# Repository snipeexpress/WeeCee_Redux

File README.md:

<!-- markdownlint-disable MD031 -->

# WeeCee Redux

**WeeCee Redux** is a hardware clone of Rasteri’s **WeeCee v0.3**, enhanced with a variety of improvements for modern usability, better component choices, and more robust design.

## Key Improvements

1. **HIDman Integration**  
   
   Replaced the legacy PS/2 port with [HIDman](https://github.com/Rasteri/HIDman), enabling support for modern USB HID devices via USB-to-PS/2 translation.

2. **Improved Audio Circuitry**  
   
   Refined the CS4237B circuitry for enhanced signal filtering and improved ground plane separation for cleaner audio performance.

3. **USB-C Power + On/Off Controller**  
   
   Replaced the micro-USB power input with USB-C. Integrated a **MAX16054** on/off controller for reliable power switching.

4. **On-Board PC Speaker**  
   
   Added a miniature PC speaker directly on the board. Can be disabled via jumper if not needed.

5. **Cost-Optimized Connectors**  
   
   Swapped out the MicroSD and audio output connectors for more affordable variants — the same ones used on Eivind Bøhler’s [TinyLlama](https://github.com/eivindbohler/TinyLlama).

6. **Enhanced Front Panel**  
   
   - Added a power button header for direct connection  
   - Added a reset button  
   - Added a power LED to indicate system status

7. **SD Card Activity Indicator**  
   
   Included circuitry and a front-panel LED to show real-time SD card activity.

8. **RTC Battery Support**  
   
   Added support for a **CR1220** coin cell battery to maintain Real-Time Clock settings.

## Enclosure Notes

This revision still fits the original enclosure used in Rasteri’s WeeCee v0.3. However, due to the added ports and indicators, **updated front and rear panels are required** for proper alignment.

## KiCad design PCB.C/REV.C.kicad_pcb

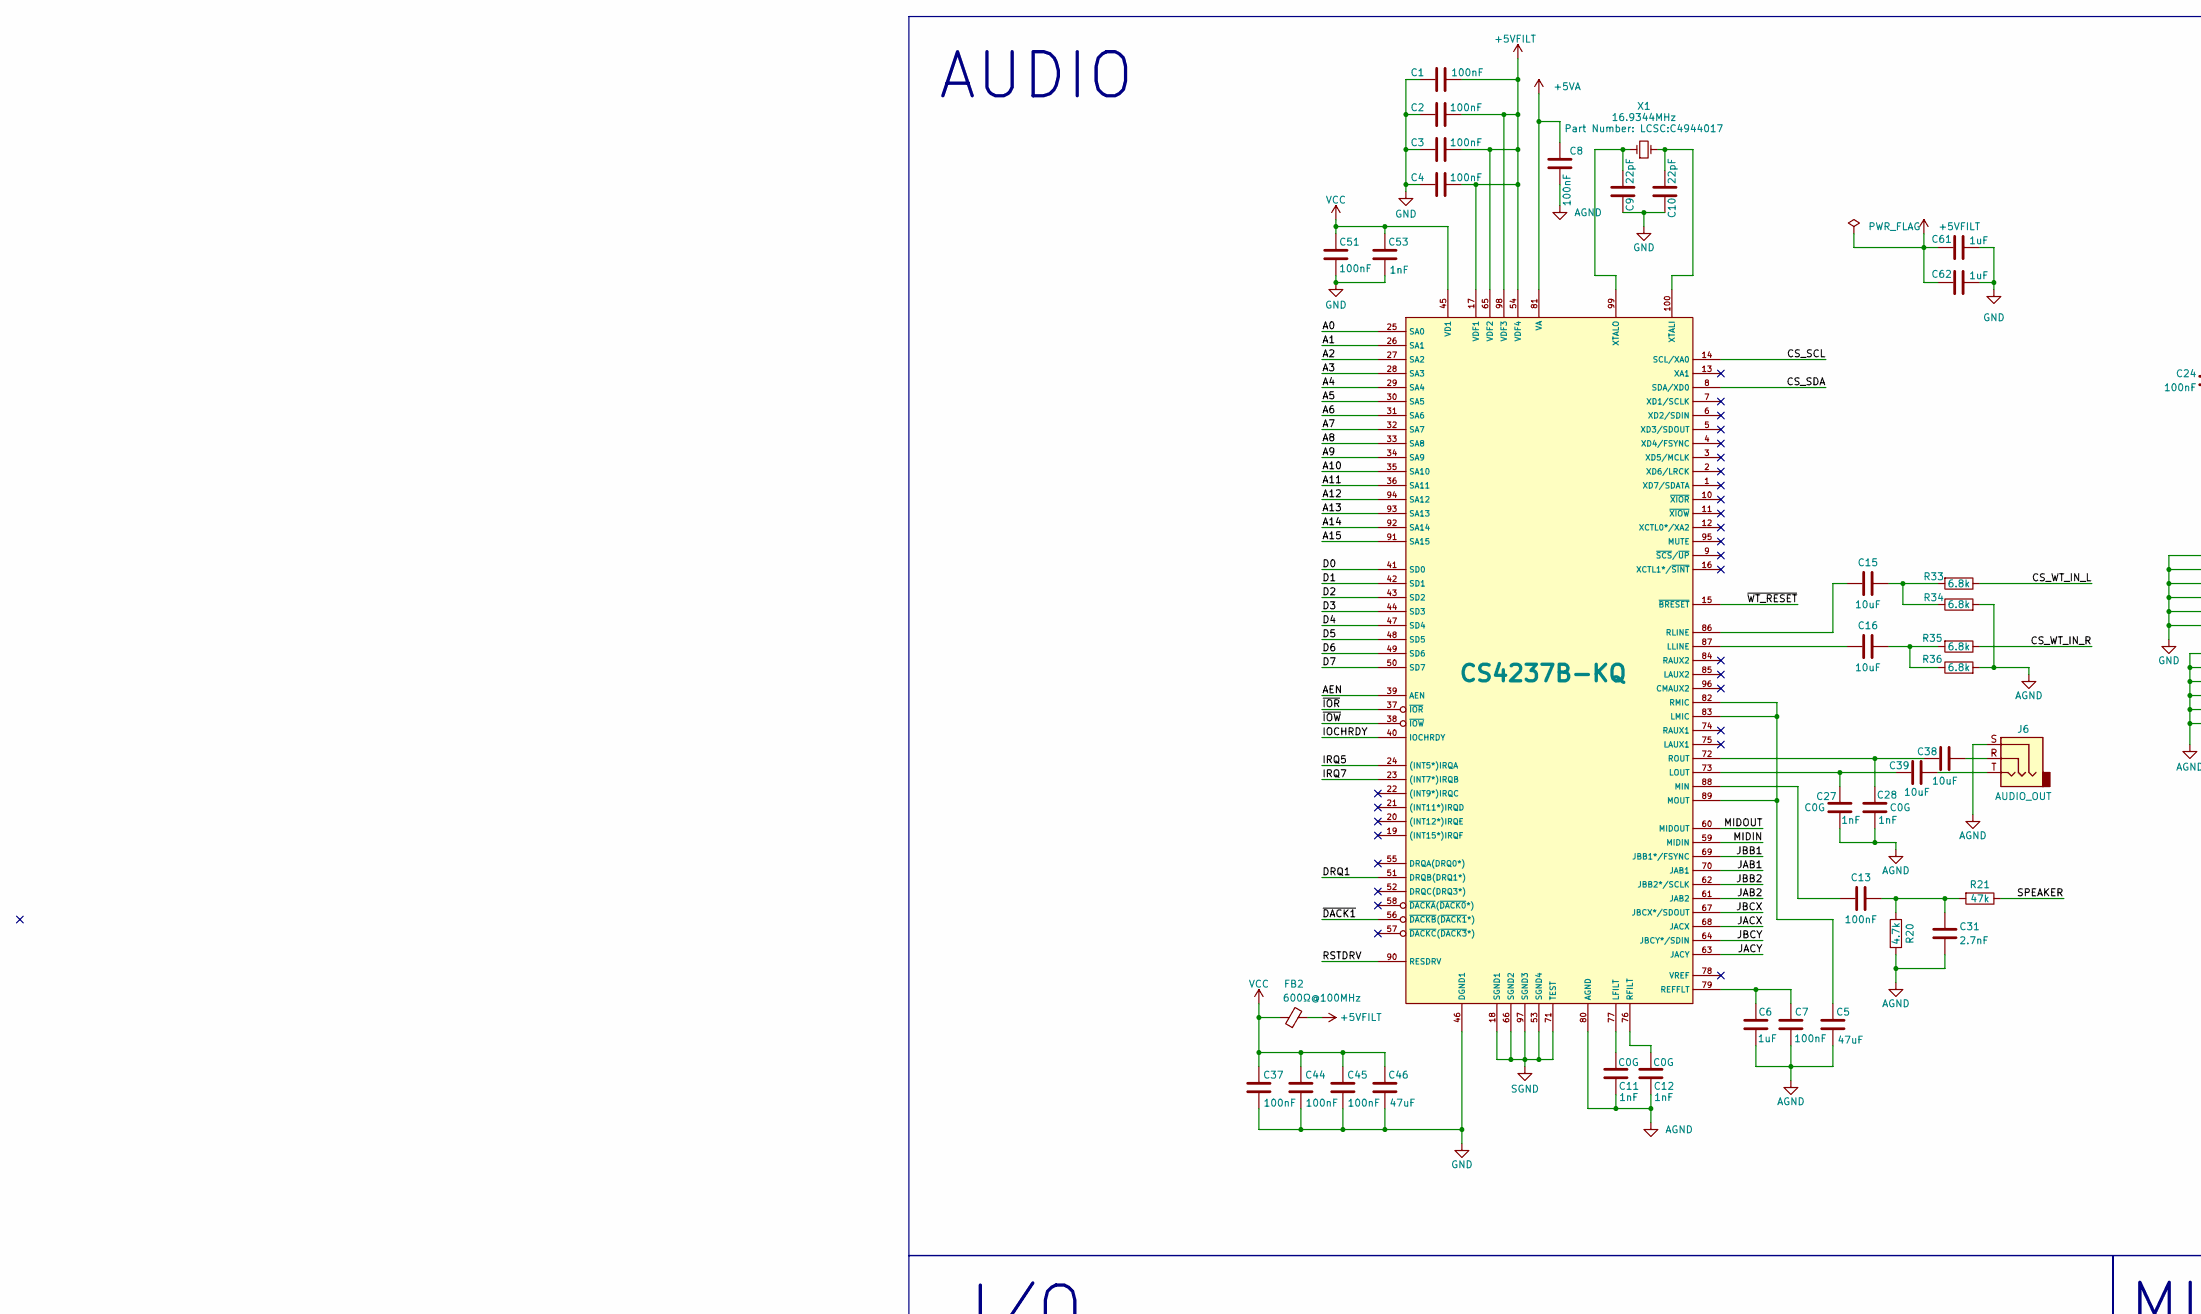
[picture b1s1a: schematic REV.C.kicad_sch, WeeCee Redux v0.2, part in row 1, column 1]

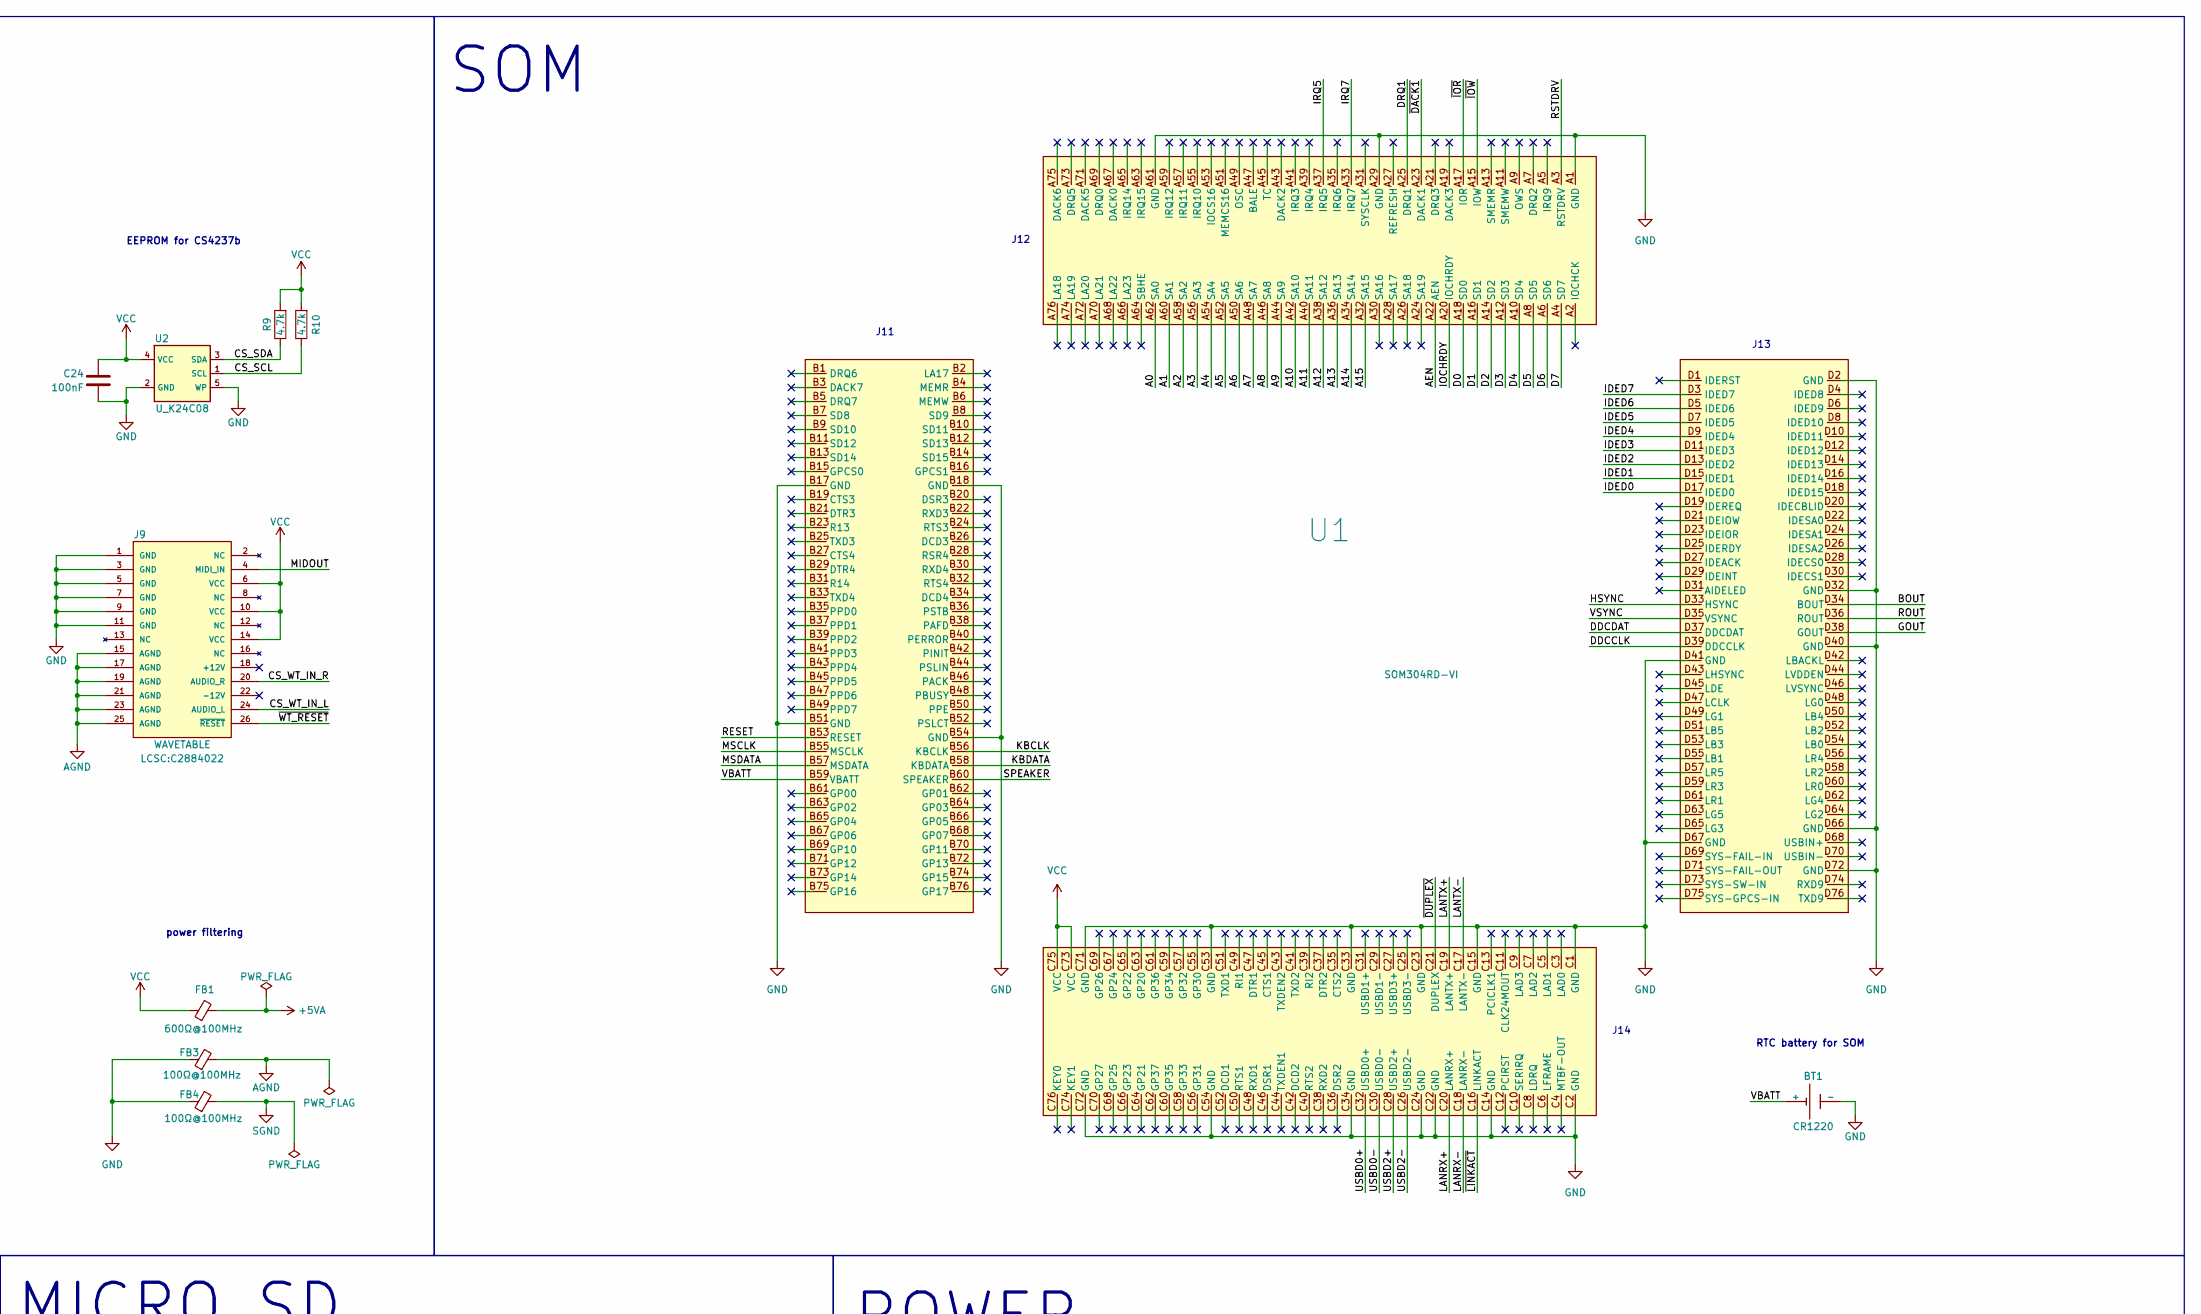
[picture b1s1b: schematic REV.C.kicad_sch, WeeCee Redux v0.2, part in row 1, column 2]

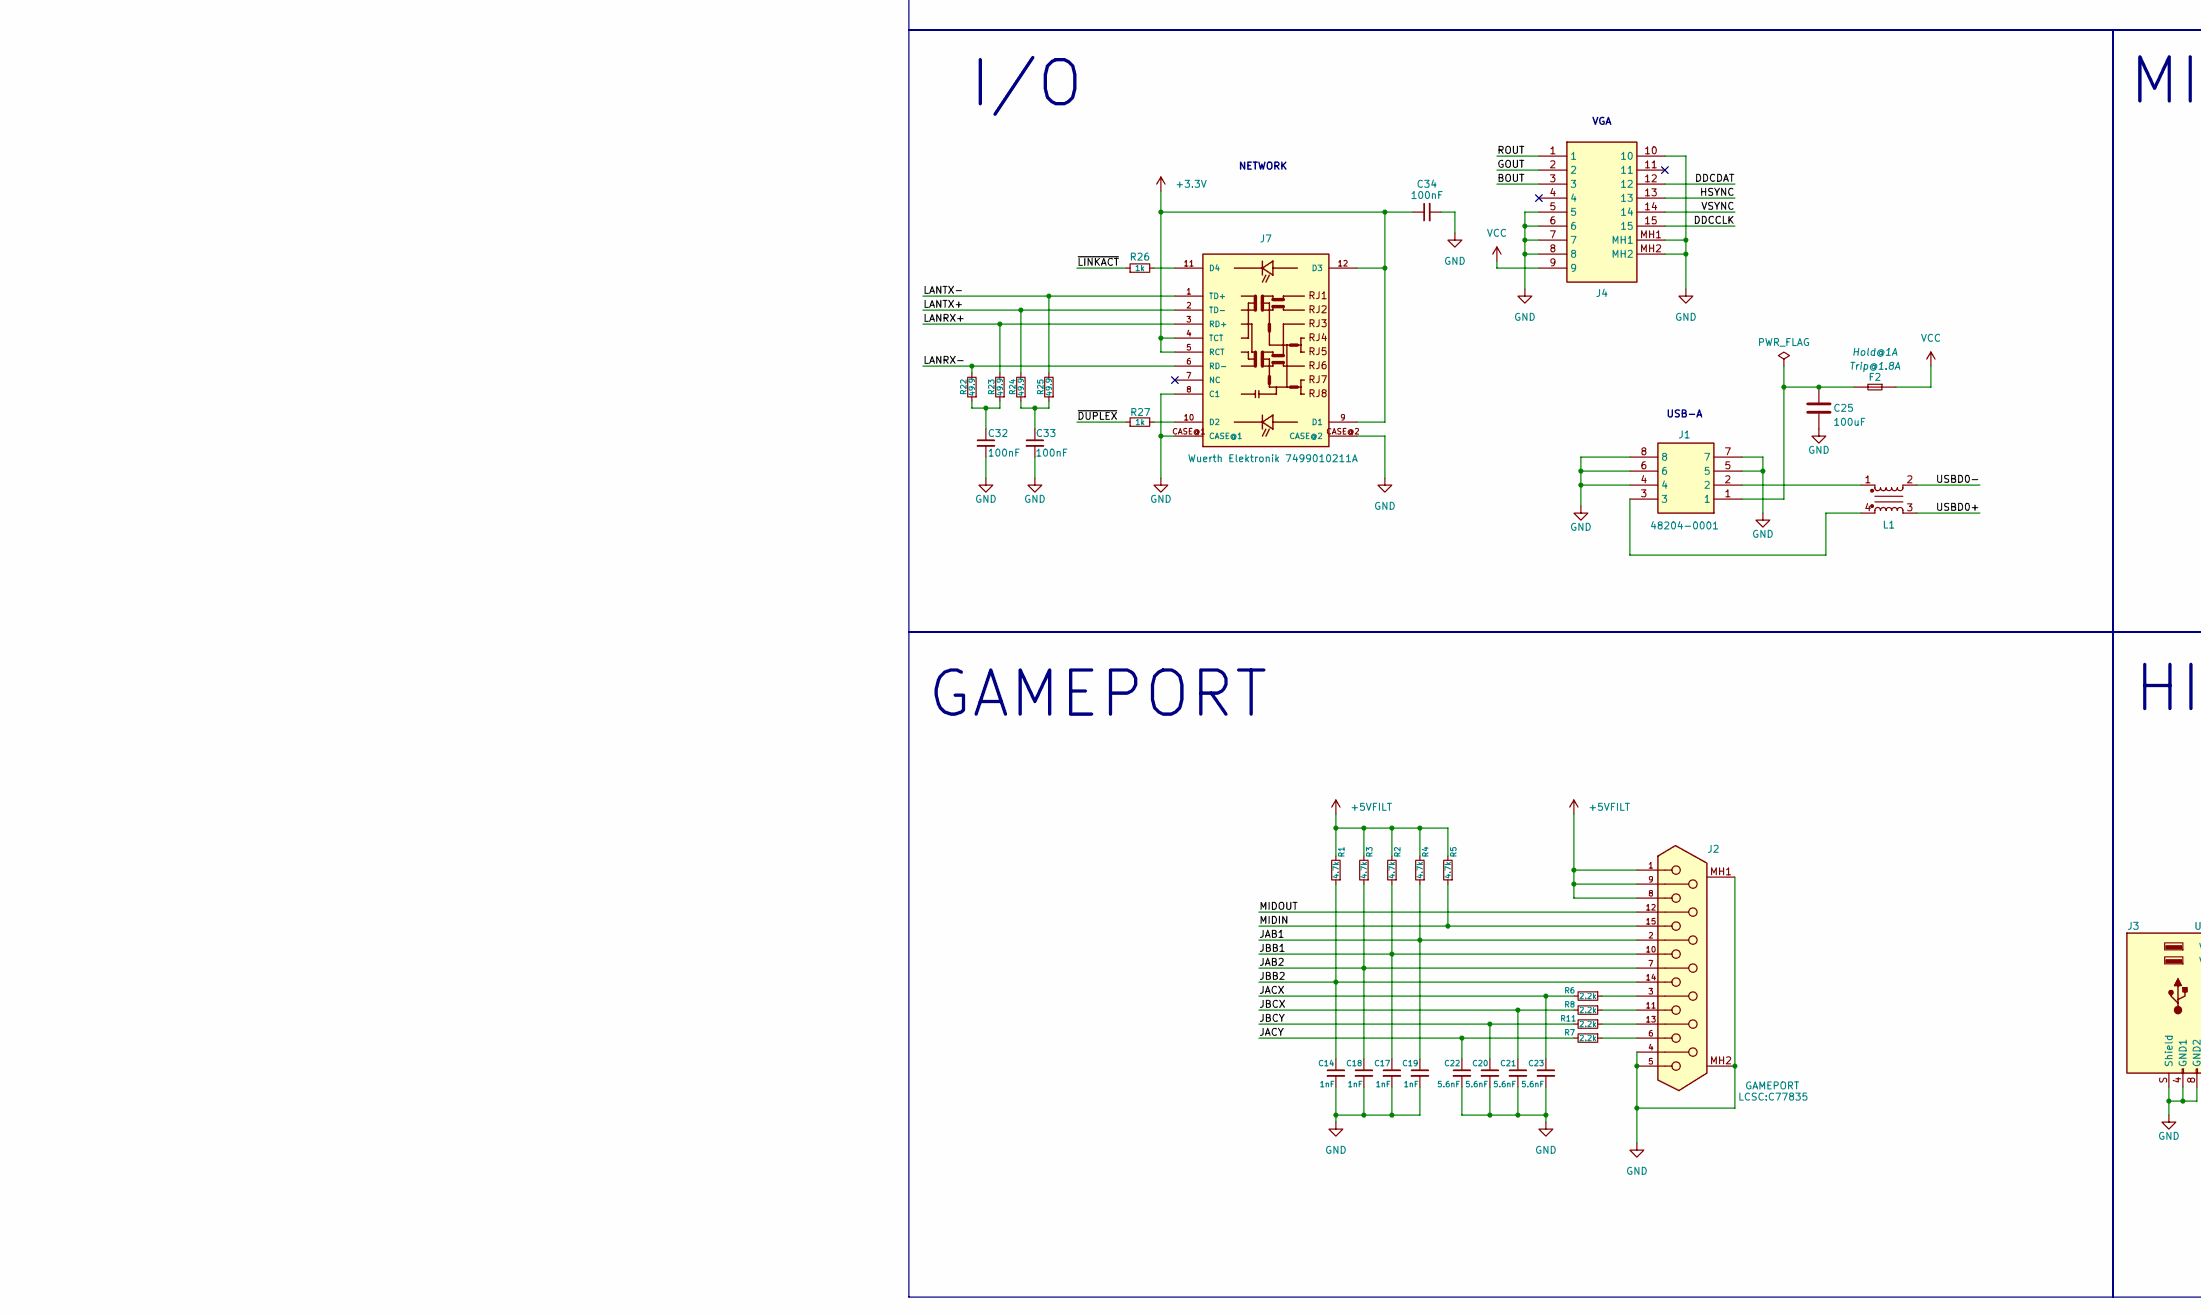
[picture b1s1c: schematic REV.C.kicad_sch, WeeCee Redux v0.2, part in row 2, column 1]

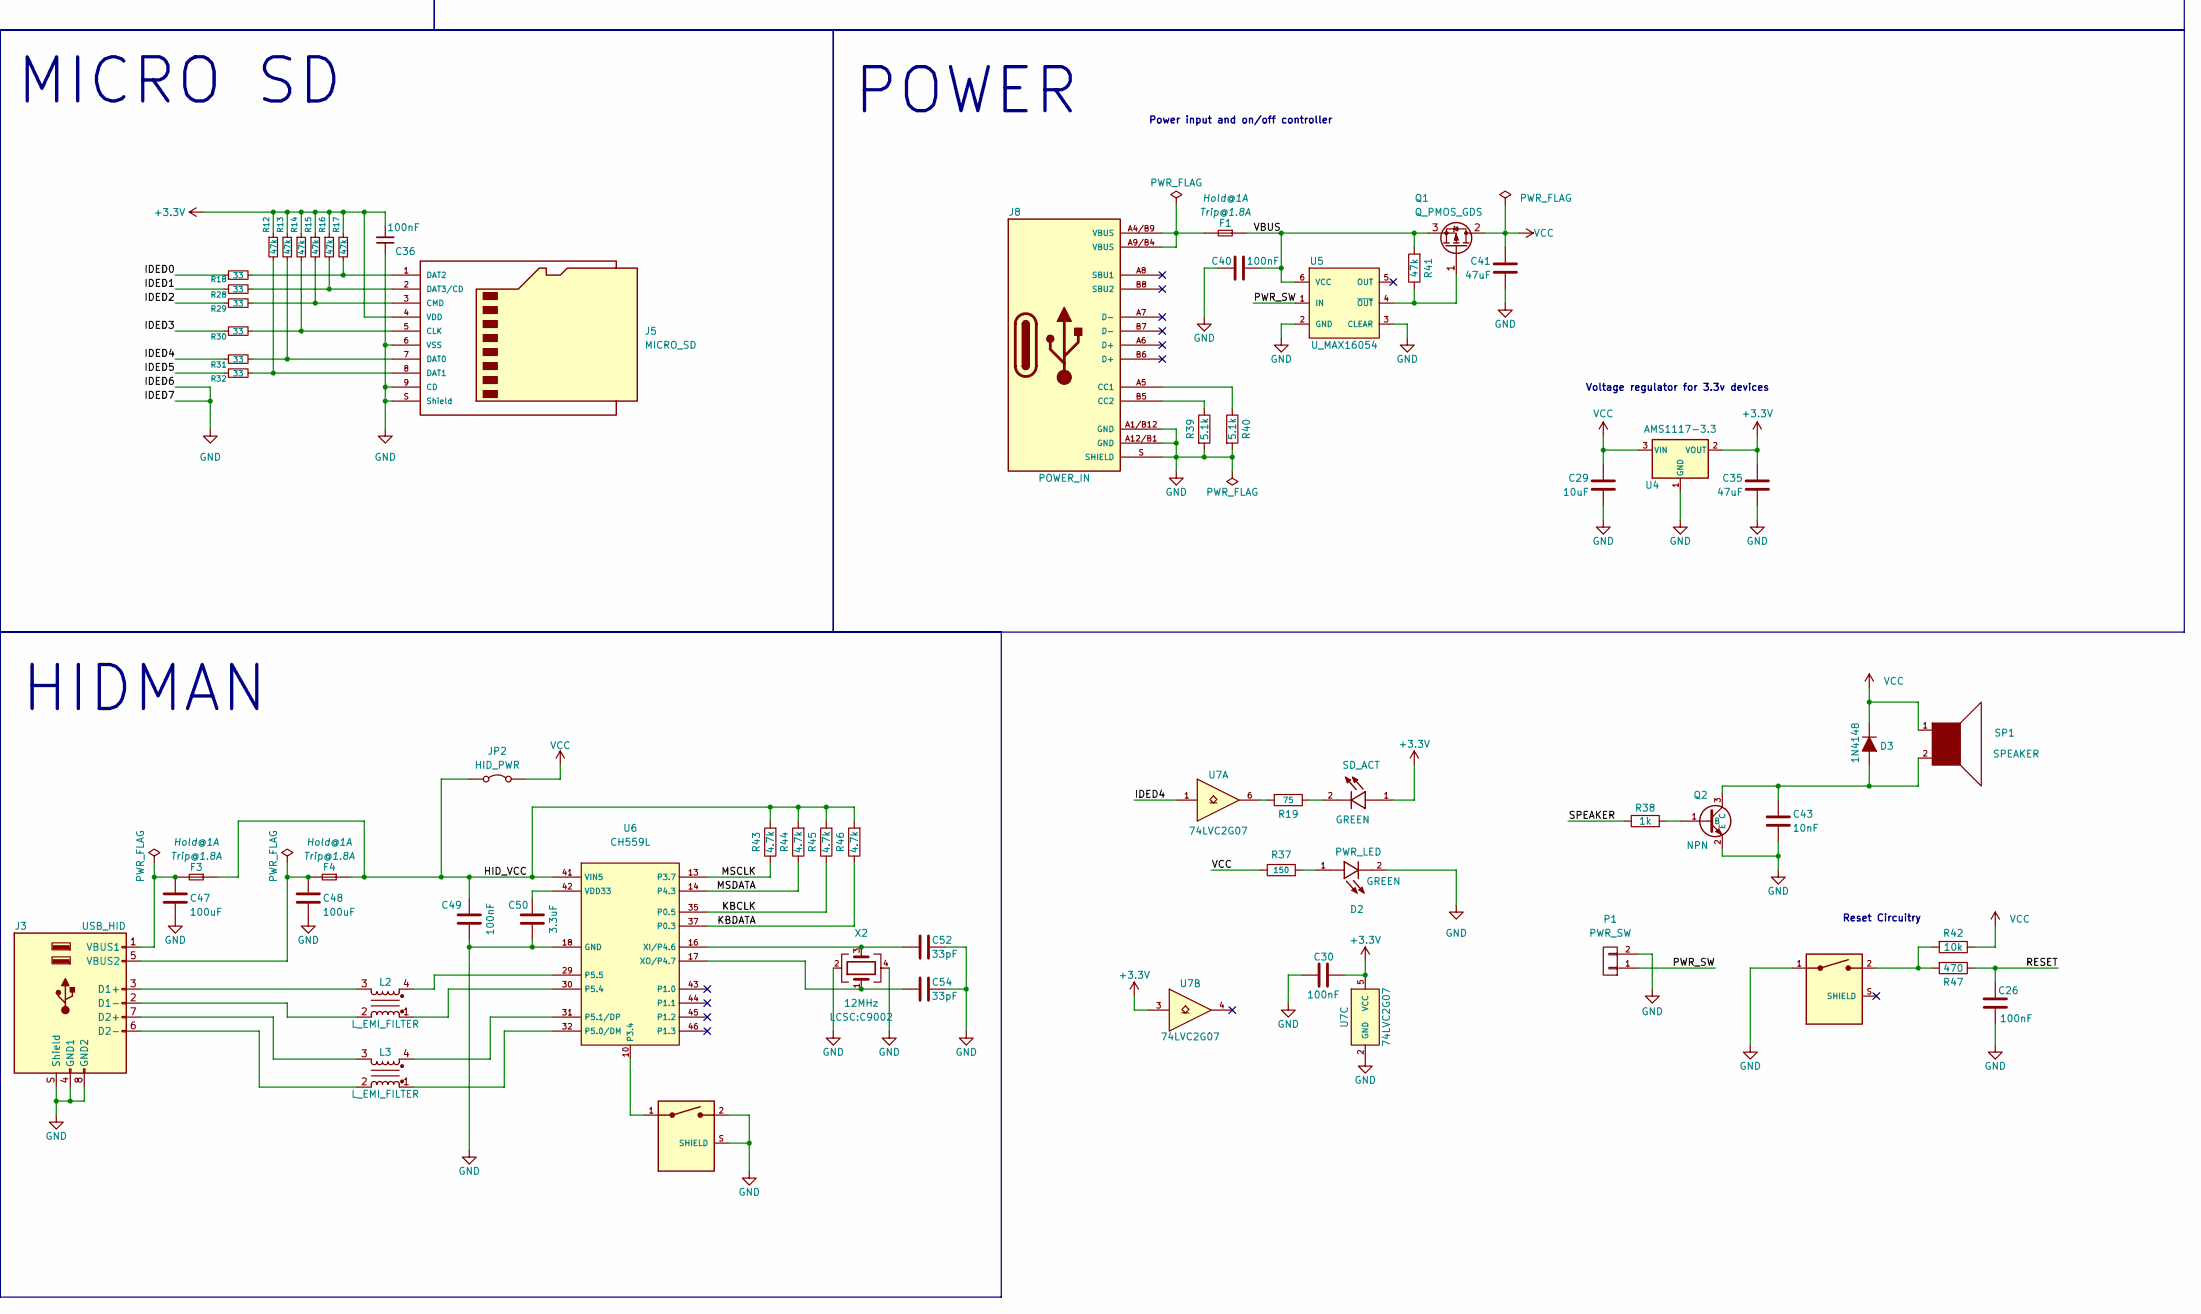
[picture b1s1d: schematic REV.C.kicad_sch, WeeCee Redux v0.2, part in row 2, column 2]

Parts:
BT1: CR1220; BATT-1220-03; Part Number LCSC:C964818
C1, C2, C3, C4, C7, C8, C13, C24, C26, C30, C32, C33, C34, C36, C37, C40, C44, C45, C49, C51: 100nF; C_0603_1608Metric; Part Number DIGIKEY:C0603C104K3RACTU
C5, C35, C41, C46: 47uF; C_1206_3216Metric; Part Number DIGIKEY:C1206C476M8PACTU
C6, C61, C62: 1uF; C_1206_3216Metric; Part Number DIGIKEY:C1206C105K3RACTU
C9, C10: 22pF; C_0603_1608Metric; Part Number DIGIKEY:C0603C220J8GACTU
C11, C12, C27, C28: 1nF; C_0603_1608Metric; Part Number DIGIKEY:GRM1885C1H102JA01D
C14, C17, C18, C19: 1nF; C_0603_1608Metric; Part Number DIGIKEY:C0603C102K3RACTU
C15, C16: 10uF; C_0603_1608Metric; Part Number DIGIKEY:C0603C106M9PACTU
C20, C21, C22, C23: 5.6nF; C_0603_1608Metric; Part Number DIGIKEY:C0603C562K3RACTU
C25, C47, C48: 100uF; C_1206_3216Metric; Part Number DIGIKEY:GRM31CR61A107MEA8K
C29: 10uF; C_1206_3216Metric; Part Number DIGIKEY:C1206C106K4PACTU
C31: 2.7nF; C_0603_1608Metric; Part Number DIGIKEY:C0603C272K5RACTU
C38, C39: 10uF; C_1206_3216Metric; Part Number DIGIKEY: C1206C106K4PACTU
C43: 10nF; C_0603_1608Metric; Part Number DIGIKEY:C0603C103K5RACTU
C50: 3.3uF; C_0603_1608Metric; Part Number DIGIKEY:C0603C335M9PACTU
C52, C54: 33pF; C_0603_1608Metric; Part Number LCSC:C1663
C53: 1nF; C_1206_3216Metric; Part Number DIGIKEY:C0603C102K5RACTU
D1: SD_ACT; LED_LTST-S220KSKT; Part Number DIGIKEY:LTST-S220KGKT
D2: PWR_LED; LED_LTST-S220KSKT; Part Number DIGIKEY:LTST-S220KGKT
D3: 1N4148; D_SOD-323F; Part Number DIGIKEY:1N4148WS-7-F
F1, F2, F3, F4: F; Fuse_0603_1608Metric_no_outline; Part Number DIGIKEY:0603L100SLYR
FB1, FB2: 600Ω@100MHz; R_0805_2012Metric; Part Number DIGIKEY:MPZ2012S601ATD25
FB3, FB4: 100Ω@100MHz; R_0805_2012Metric; Part Number DIGIKEY:MPZ2012S101AT000
J1: 48204-0001; USB-A_1P_VERTICAL; Part Number DIGIKEY:0482040001
J2: GAMEPORT; 57478454; Part Number LCSC:C77835
J3: USB_HID; USB-A_2P_STACKED; Part Number DIGIKEY:C12049
J4: VGA_IN; 634015263032; Part Number DIGIKEY:634-015-263-032
J5: MICRO_SD; MicroSD_TF01A_overhang; Part Number LCSC:C91145
J6: AUDIO_OUT; J_AUDIO35_C95463; Part Number LCSC:C95463
J7: Wuerth Elektronik 7499010211A; NIC_single_port_TH; Part Number DIGIKEY:7499010211A
J8: POWER_IN; USB-C_31-M-12; Part Number LCSC:C165948
J9: WAVETABLE; J_CONN_02X13; Part Number LCSC:C2884022
JP2: HID_PWR; SolderJumper-2_P1.3mm_Open_RoundedPad1.0x1.5mm
L1, L2, L3: L_EMI_FILTER; L_EMI_FILTER_MCM2012B900GBE; Part Number DIGIKEY:MCM2012B900GBEDG
P1: PWR_SW; PinHeader_1x02_P2.00mm_Horizontal; Part Number ALIEXPRESS
Q1: Q_PMOS_GDS; Q_PFET_ENH_SOT-23-3; Part Number DIGIKEY:DMP3099L-7
Q2: NPN; Q_PFET_ENH_SOT-23-3; Part Number LCSC:C2146
R1, R2, R3, R4, R5, R9, R10, R20, R43, R44, R45, R46: 4.7k; R_0603_1608Metric; Part Number DIGIKEY:RC0603FR-074K7L
R6, R7, R8, R11: 2.2k; R_0603_1608Metric; Part Number DIGIKEY:RC0603FR-072K2L
R12, R13, R14, R15, R16, R17, R21, R41: 47k; R_0603_1608Metric; Part Number DIGIKEY:RC0603FR-0747KL
R18, R28, R29, R30, R31, R32: 33; R_0603_1608Metric; Part Number DIGIKEY:RC0603JR-0733RL
R19: 75; R_0603_1608Metric; Part Number DIGIKEY:RC0603JR-0775RL
R22, R23, R24, R25: 49.9; R_0603_1608Metric; Part Number DIGIKEY:RC0603FR-0749R9L
R26, R27, R38: 1k; R_0603_1608Metric; Part Number DIGIKEY:RC0603FR-071KL
R33, R34, R35, R36: 6.8k; R_0603_1608Metric; Part Number DIGIKEY:RC0603JR-076K8L
R37: 150; R_0603_1608Metric; Part Number DIGIKEY:RC0603FR-07150RL
R39, R40: 5.1k; R_0603_1608Metric; Part Number DIGIKEY:RC0603FR-075K1L
R42: 10k; R_0603_1608Metric; Part Number DIGIKEY:RC0603FR-0710KL
R47: 470; R_0603_1608Metric; Part Number DIGIKEY:RC0603JR-07470RL
SP1: SPEAKER; SP; Part Number DIGIKEY:SP3243EEA-L/TR
SW2: RESET; SW_C2859426; Part Number LCSC:C2859426
SW3: HID_PRG; SW_C2859426; Part Number LCSC:C2859426
U1: SOM304RD-VI; Part Number ICOP
U2: U_K24C08; U_SOT-23-5; Part Number DIGIKEY:24LC08BT-I/OT
U3: CS4237B-KQ; U_TQFP-100_14x14mm_P0.5mm_HandSoldering; Part Number UTSOURCE
U4: AMS1117-3.3; U_SOT-223-3; Part Number DIGIKEY:AMS1117-3.3
U5: U_MAX16054; U_TSOT-23-6; Part Number DIGIKEY:MAX16054AZT+T
U6: CH559L; U_QFP-48-0.5mm; Part Number LCSC:C150548
U7: 74LVC2G07; U_SOT-363_SC-70-6; Part Number DIGIKEY:SN74LVC2G07DCKR
X1: 16.9344MHz; X_Crystal_SMD_HC49S-MINI; Part Number LCSC:C4944017
X2: 12MHz; X_SMD3225; Part Number LCSC:C9002

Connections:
+3.3V: C30.1, C34.1, C35.1, C36.2, D1.1, J5.4 (VDD), J7.4 (TCT), J7.5 (RCT), J7.9 (D1), J7.12 (D3), R12.1, R13.1, R14.1, R15.1, R16.1, R17.1, U4.2 (VOUT), U7.3, U7.5 (VCC)
+5VA: C8.2, FB1.2, U3.81 (VA)
+5VFILT: C1.1, C2.1, C3.1, C4.1, C61.2, C62.2, FB2.2, J2.1, J2.8, J2.9, R1.2, R2.2, R3.2, R4.2, R5.2, U3.17 (VDF1), U3.54 (VDF4), U3.65 (VDF2), U3.98 (VDF3)
/A0: U1.A62 (SA0), U3.25 (SA0)
/A1: U1.A60 (SA1), U3.26 (SA1)
/A2: U1.A58 (SA2), U3.27 (SA2)
/A3: U1.A56 (SA3), U3.28 (SA3)
/A4: U1.A54 (SA4), U3.29 (SA4)
/A5: U1.A52 (SA5), U3.30 (SA5)
/A6: U1.A50 (SA6), U3.31 (SA6)
/A7: U1.A48 (SA7), U3.32 (SA7)
/A8: U1.A46 (SA8), U3.33 (SA8)
/A9: U1.A44 (SA9), U3.34 (SA9)
/A10: U1.A42 (SA10), U3.35 (SA10)
/A11: U1.A40 (SA11), U3.36 (SA11)
/A12: U1.A38 (SA12), U3.94 (SA12)
/A13: U1.A36 (SA13), U3.93 (SA13)
/A14: U1.A34 (SA14), U3.92 (SA14)
/A15: U1.A32 (SA15), U3.91 (SA15)
/AEN: U1.A22 (AEN), U3.39 (AEN)
/BOUT: J4.3, U1.D34 (BOUT)
/CS_SCL: R10.1, U2.1 (SCL), U3.14 (SCL/XA0)
/CS_SDA: R9.1, U2.3 (SDA), U3.8 (SDA/XD0)
/CS_WT_IN_L: J9.24 (AUDIO_L), R33.1
/CS_WT_IN_R: J9.20 (AUDIO_R), R35.1
/D0: U1.A18 (SD0), U3.41 (SD0)
/D1: U1.A16 (SD1), U3.42 (SD1)
/D2: U1.A14 (SD2), U3.43 (SD2)
/D3: U1.A12 (SD3), U3.44 (SD3)
/D4: U1.A10 (SD4), U3.47 (SD4)
/D5: U1.A8 (SD5), U3.48 (SD5)
/D6: U1.A6 (SD6), U3.49 (SD6)
/D7: U1.A4 (SD7), U3.50 (SD7)
/DDCCLK: J4.15, U1.D39 (DDCCLK)
/DDCDAT: J4.12, U1.D37 (DDCDAT)
/DRQ1: U1.A25 (DRQ1), U3.51 (DRQB(DRQ1*))
/GOUT: J4.2, U1.D38 (GOUT)
/HID_VCC: C49.2, F3.1, F4.1, JP2.1 (A), R43.2, R44.2, R45.2, R46.2, U6.41 (VIN5)
/HSYNC: J4.13, U1.D33 (HSYNC)
/IDED0: R18.1, U1.D17 (IDED0)
/IDED1: R28.1, U1.D15 (IDED1)
/IDED2: R29.1, U1.D13 (IDED2)
/IDED3: R30.1, U1.D11 (IDED3)
/IDED4: R31.1, U1.D9 (IDED4), U7.1
/IDED5: R32.1, U1.D7 (IDED5)
/IOCHRDY: U1.A20 (IOCHRDY), U3.40 (IOCHRDY)
/IRQ5: U1.A37 (IRQ5), U3.24 ((INT5*)IRQA)
/IRQ7: U1.A33 (IRQ7), U3.23 ((INT7*)IRQB)
/JAB1: C19.1, J2.2, R4.1, U3.70 (JAB1)
/JAB2: C18.1, J2.7, R3.1, U3.61 (JAB2)
/JACX: C23.1, R6.2, U3.68 (JACX)
/JACY: C22.1, R7.2, U3.63 (JACY)
/JBB1: C17.1, J2.10, R2.1, U3.69 (JBB1*/FSYNC)
/JBB2: C14.1, J2.14, R1.1, U3.62 (JBB2*/SCLK)
/JBCX: C21.1, R8.2, U3.67 (JBCX*/SDOUT)
/JBCY: C20.1, R11.2, U3.64 (JBCY*/SDIN)
/KBCLK: R45.1, U1.B56 (KBCLK), U6.35 (P0.5)
/KBDATA: R46.1, U1.B58 (KBDATA), U6.37 (P0.3)
/LANRX+: J7.3 (RD+), R23.2, U1.C20 (LANRX+)
/LANRX-: J7.6 (RD-), R22.2, U1.C18 (LANRX-)
/LANTX+: J7.2 (TD-), R24.2, U1.C19 (LANTX+)
/LANTX-: J7.1 (TD+), R25.2, U1.C17 (LANTX-)
/MIDIN: J2.15, R5.1, U3.59 (MIDIN)
/MIDOUT: J2.12, J9.4 (MIDI_IN), U3.60 (MIDOUT)
/MSCLK: R43.1, U1.B55 (MSCLK), U6.13 (P3.7)
/MSDATA: R44.1, U1.B57 (MSDATA), U6.14 (P4.3)
/PWR_SW: P1.1, U5.1 (IN)
/RESET: C26.2, R47.1, U1.B53 (RESET)
/ROUT: J4.1, U1.D36 (ROUT)
/RSTDRV: U1.A3 (RSTDRV), U3.90 (RESDRV)
/SPEAKER: R21.1, R38.1, U1.B60 (SPEAKER)
/USBD0+: L1.3, U1.C32 (USBD0+)
/USBD0-: L1.2, U1.C30 (USBD0-)
/USBD2+: U1.C28 (USBD2+)
/USBD2-: U1.C26 (USBD2-)
/VBATT: BT1.1 (+), U1.B59 (VBATT)
/VBUS: C40.2, F1.1, Q1.3 (S), R41.2, U5.6 (VCC)
/VSYNC: J4.14, U1.D35 (VSYNC)
/~DACK1: U1.A23 (DACK1), U3.56 (~DACKB(~DACK1*))
/~DUPLEX: R27.1, U1.C21 (DUPLEX)
/~IOR: U1.A17 (IOR), U3.37 (~IOR)
/~IOW: U1.A15 (IOW), U3.38 (~IOW)
/~LINKACT: R26.1, U1.C16 (LINKACT)
/~WT_RESET: J9.26 (~RESET), U3.15 (~BRESET)
AGND: C5.2, C6.2, C7.2, C8.1, C11.1, C12.1, C27.2, C28.2, C31.2, FB3.2, J6.S, J9.15 (AGND), J9.17 (AGND), J9.19 (AGND), J9.21 (AGND), J9.23 (AGND), J9.25 (AGND), R20.2, R34.2, R36.2, U3.80 (AGND)
GND: BT1.2 (-), C1.2, C2.2, C3.2, C4.2, C9.1, C10.1, C14.2, C17.2, C18.2, C19.2, C20.2, C21.2, C22.2, C23.2, C24.2, C25.2, C26.1, C29.2, C30.2, C32.2, C33.2, C34.2, C35.2, C36.1, C37.1, C40.1, C41.2, C43.2, C44.1, C45.1, C46.2, C47.2, C48.2, C49.1, C50.1, C51.2, C52.2, C53.2, C54.2, C61.1, C62.1, D2.2, FB3.1, FB4.1, J1.4, J1.5, J1.6, J1.7, J1.8, J2.4, J2.5, J2.MH1, J2.MH2, J3.4 (GND1), J3.8 (GND2), J3.S (Shield), J4.5, J4.6, J4.7, J4.8, J4.10, J4.MH1, J4.MH2, J5.6 (VSS), J5.9 (CD), J5.S (Shield), J7.8 (C1), J7.CASE@1, J7.CASE@2, J8.A1/B12 (GND), J8.A12/B1 (GND), J8.S (SHIELD), J9.1 (GND), J9.3 (GND), J9.5 (GND), J9.7 (GND), J9.9 (GND), J9.11 (GND), P1.2, Q2.2 (E), R39.2, R40.2, SW2.1, SW3.2, SW3.S (SHIELD), U1.A1 (GND), U1.A29 (GND), U1.A61 (GND), U1.B17 (GND), U1.B18 (GND), U1.B51 (GND), U1.B54 (GND), U1.C1 (GND), U1.C2 (GND), U1.C14 (GND), U1.C15 (GND), U1.C22 (GND), U1.C23 (GND), U1.C24 (GND), U1.C33 (GND), U1.C34 (GND), U1.C53 (GND), U1.C54 (GND), U1.C71 (GND), U1.C72 (GND), U1.D2 (GND), U1.D3 (IDED7), U1.D5 (IDED6), U1.D32 (GND), U1.D40 (GND), U1.D41 (GND), U1.D66 (GND), U1.D67 (GND), U1.D72 (GND), U2.2 (GND), U2.5 (WP), U3.46 (DGND1), U4.1 (GND), U5.2 (GND), U5.3 (CLEAR), U6.18 (GND), U7.2 (GND), X2.2, X2.4
unnamed: C13.2, C31.1, R20.1, R21.2
unnamed: C15.2, R33.2, R34.1
unnamed: C16.2, R35.2, R36.1
unnamed: C25.1, F2.2, J1.1
unnamed: C32.1, R22.1, R23.1
unnamed: C33.1, R24.1, R25.1
unnamed: C38.2, J6.R
unnamed: C39.2, J6.T
unnamed: D1.2, R19.1
unnamed: D2.1, R37.2
unnamed: C43.1, D3.2 (A), Q2.3 (C), SP1.2
unnamed: F1.2, J8.A4/B9 (VBUS), J8.A9/B4 (VBUS)
unnamed: J1.2, L1.1
unnamed: J1.3, L1.4
unnamed: J2.3, R6.1
unnamed: J2.6, R7.1
unnamed: J2.11, R8.1
unnamed: J2.13, R11.1
unnamed: J3.3 (D1+), L2.3
unnamed: J3.2 (D1-), L2.2
unnamed: J3.7 (D2+), L3.3
unnamed: J3.6 (D2-), L3.2
unnamed: C47.1, F3.2, J3.1 (VBUS1)
unnamed: C48.1, F4.2, J3.5 (VBUS2)
unnamed: J5.5 (CLK), R14.2, R30.2
unnamed: J5.3 (CMD), R15.2, R29.2
unnamed: J5.7 (DAT0), R13.2, R31.2
unnamed: J5.8 (DAT1), R12.2, R32.2
unnamed: J5.1 (DAT2), R17.2, R18.2
unnamed: J5.2 (DAT3/CD), R16.2, R28.2
unnamed: J7.10 (D2), R27.2
unnamed: J7.11 (D4), R26.2
unnamed: J8.A5 (CC1), R40.1
unnamed: J8.B5 (CC2), R39.1
unnamed: Q1.1 (G), R41.1, U5.4 (~OUT)
unnamed: Q2.1 (B), R38.2
unnamed: R19.2, U7.6
unnamed: R42.2, R47.2, SW2.2
unnamed: C11.2, U3.77 (LFILT)
unnamed: C16.1, U3.87 (LLINE)
unnamed: C5.1, U3.82 (RMIC), U3.83 (LMIC), U3.89 (MOUT)
unnamed: C27.1, C39.1, U3.73 (LOUT)
unnamed: C13.1, U3.88 (MIN)
unnamed: C6.1, C7.1, U3.79 (REFFLT)
unnamed: C12.2, U3.76 (RFILT)
unnamed: C15.1, U3.86 (RLINE)
unnamed: C28.1, C38.1, U3.72 (ROUT)
unnamed: C10.2, U3.100 (XTALI), X1.2
unnamed: C9.2, U3.99 (XTALO), X1.1
unnamed: SW3.1, U6.10 (P3.4)
unnamed: L3.1, U6.32 (P5.0/DM)
unnamed: L3.4, U6.31 (P5.1/DP)
unnamed: L2.1, U6.30 (P5.4)
unnamed: L2.4, U6.29 (P5.5)
unnamed: C50.2, U6.42 (VDD33)
unnamed: C52.1, U6.16 (XI/P4.6), X2.3
unnamed: C54.1, U6.17 (XO/P4.7), X2.1
SGND: FB4.2, U3.18 (SGND1), U3.53 (SGND4), U3.66 (SGND2), U3.71 (TEST), U3.97 (SGND3)
VCC: C24.1, C29.1, C37.2, C41.1, C44.2, C45.2, C46.1, C51.1, C53.1, D3.1 (K), F2.1, FB1.1, FB2.1, J4.9, J9.6 (VCC), J9.10 (VCC), J9.14 (VCC), JP2.2 (B), Q1.2 (D), R9.2, R10.2, R37.1, R42.1, SP1.1, U1.C73 (VCC), U1.C75 (VCC), U2.4 (VCC), U3.45 (VD1), U4.3 (VIN)

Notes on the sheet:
POWER
J13
MICRO SD
GAMEPORT
AUDIO
RTC battery for SOM
J11
J14
VGA
J12
Voltage regulator for 3.3v devices
Power input and on/off controller
Reset Circuitry
HIDMAN
power filtering
NETWORK
I/O
EEPROM for CS4237b
SOM
USB-A

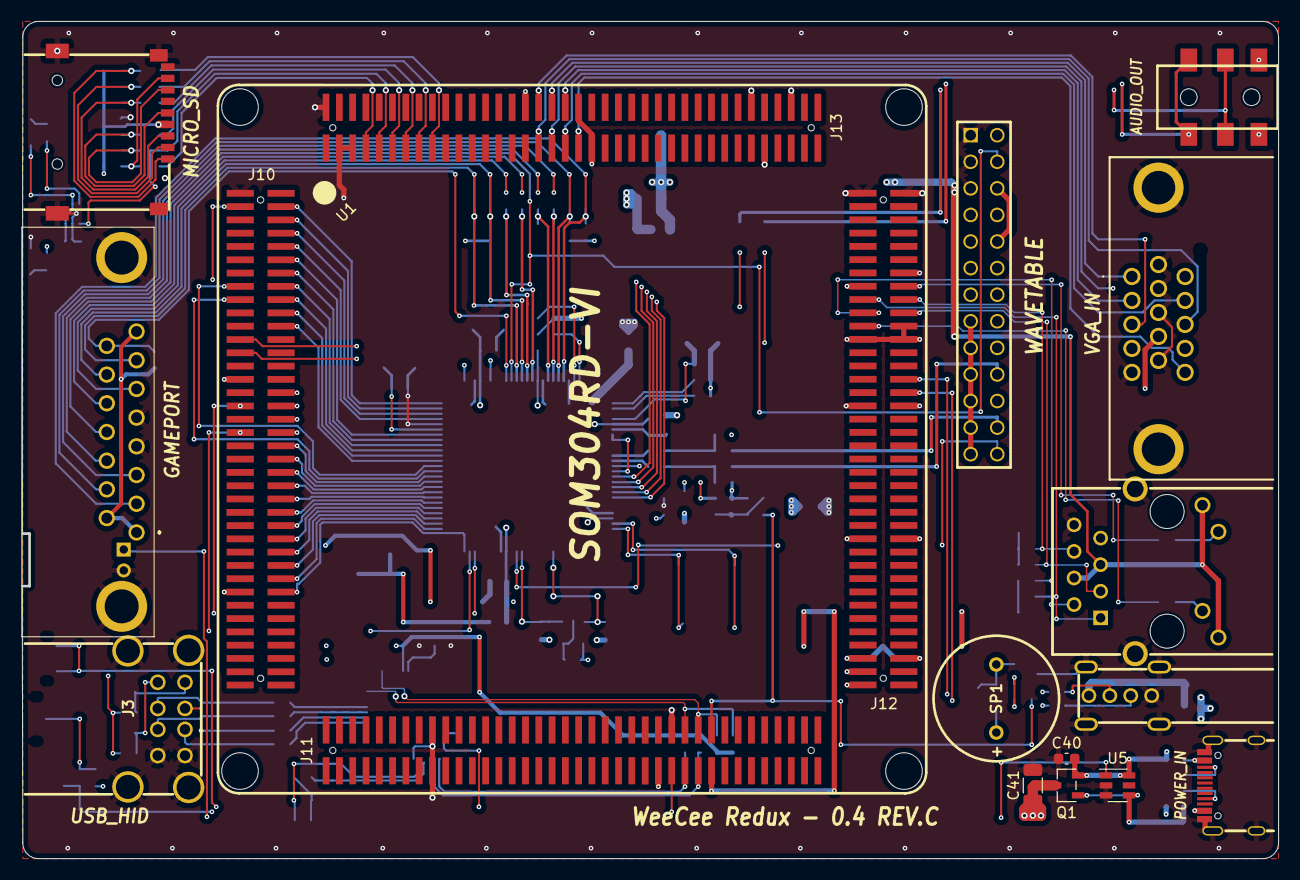
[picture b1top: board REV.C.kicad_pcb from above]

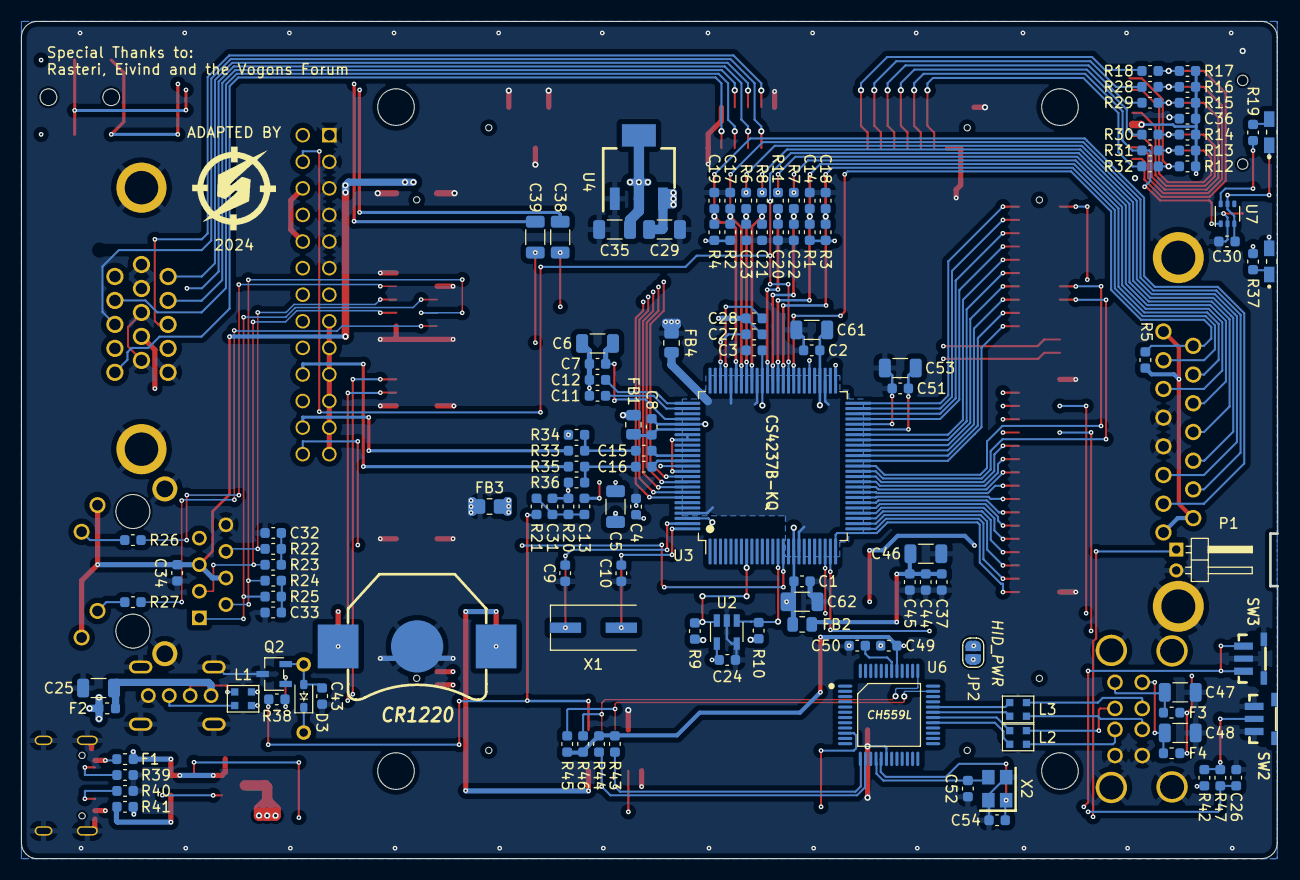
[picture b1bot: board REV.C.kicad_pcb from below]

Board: 4 copper layers, 120.0 x 80.0 mm, 143 parts (128 on the bottom side), 143 nets.

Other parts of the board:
2024: 2024; snipe_96x96px

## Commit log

2025-05-27 250527_1
    cleaned up BOM
2025-05-28 250528_01
    most recent backup
2025-05-29 Create LICENSE
